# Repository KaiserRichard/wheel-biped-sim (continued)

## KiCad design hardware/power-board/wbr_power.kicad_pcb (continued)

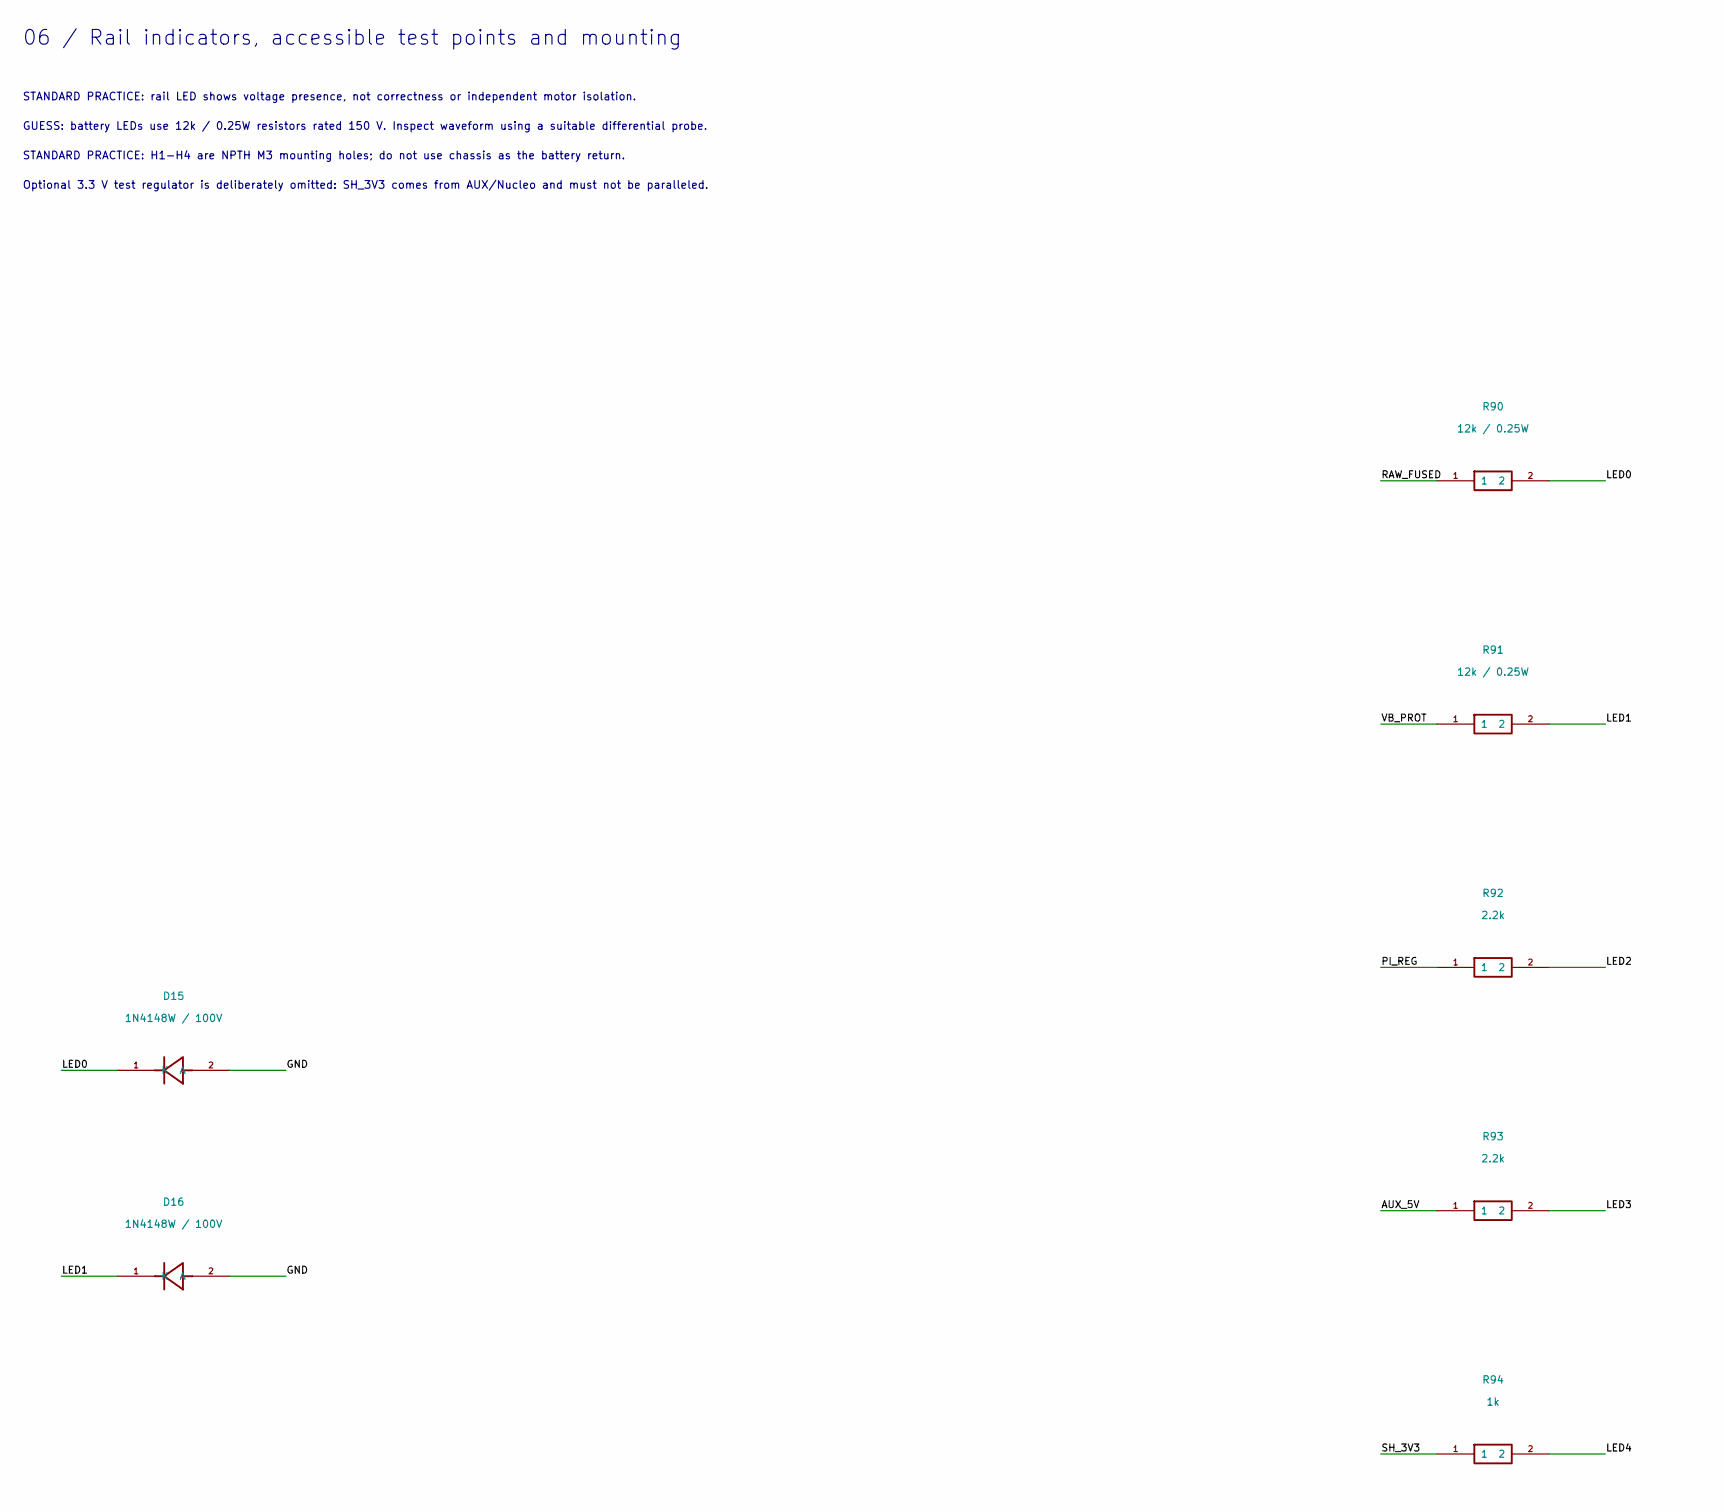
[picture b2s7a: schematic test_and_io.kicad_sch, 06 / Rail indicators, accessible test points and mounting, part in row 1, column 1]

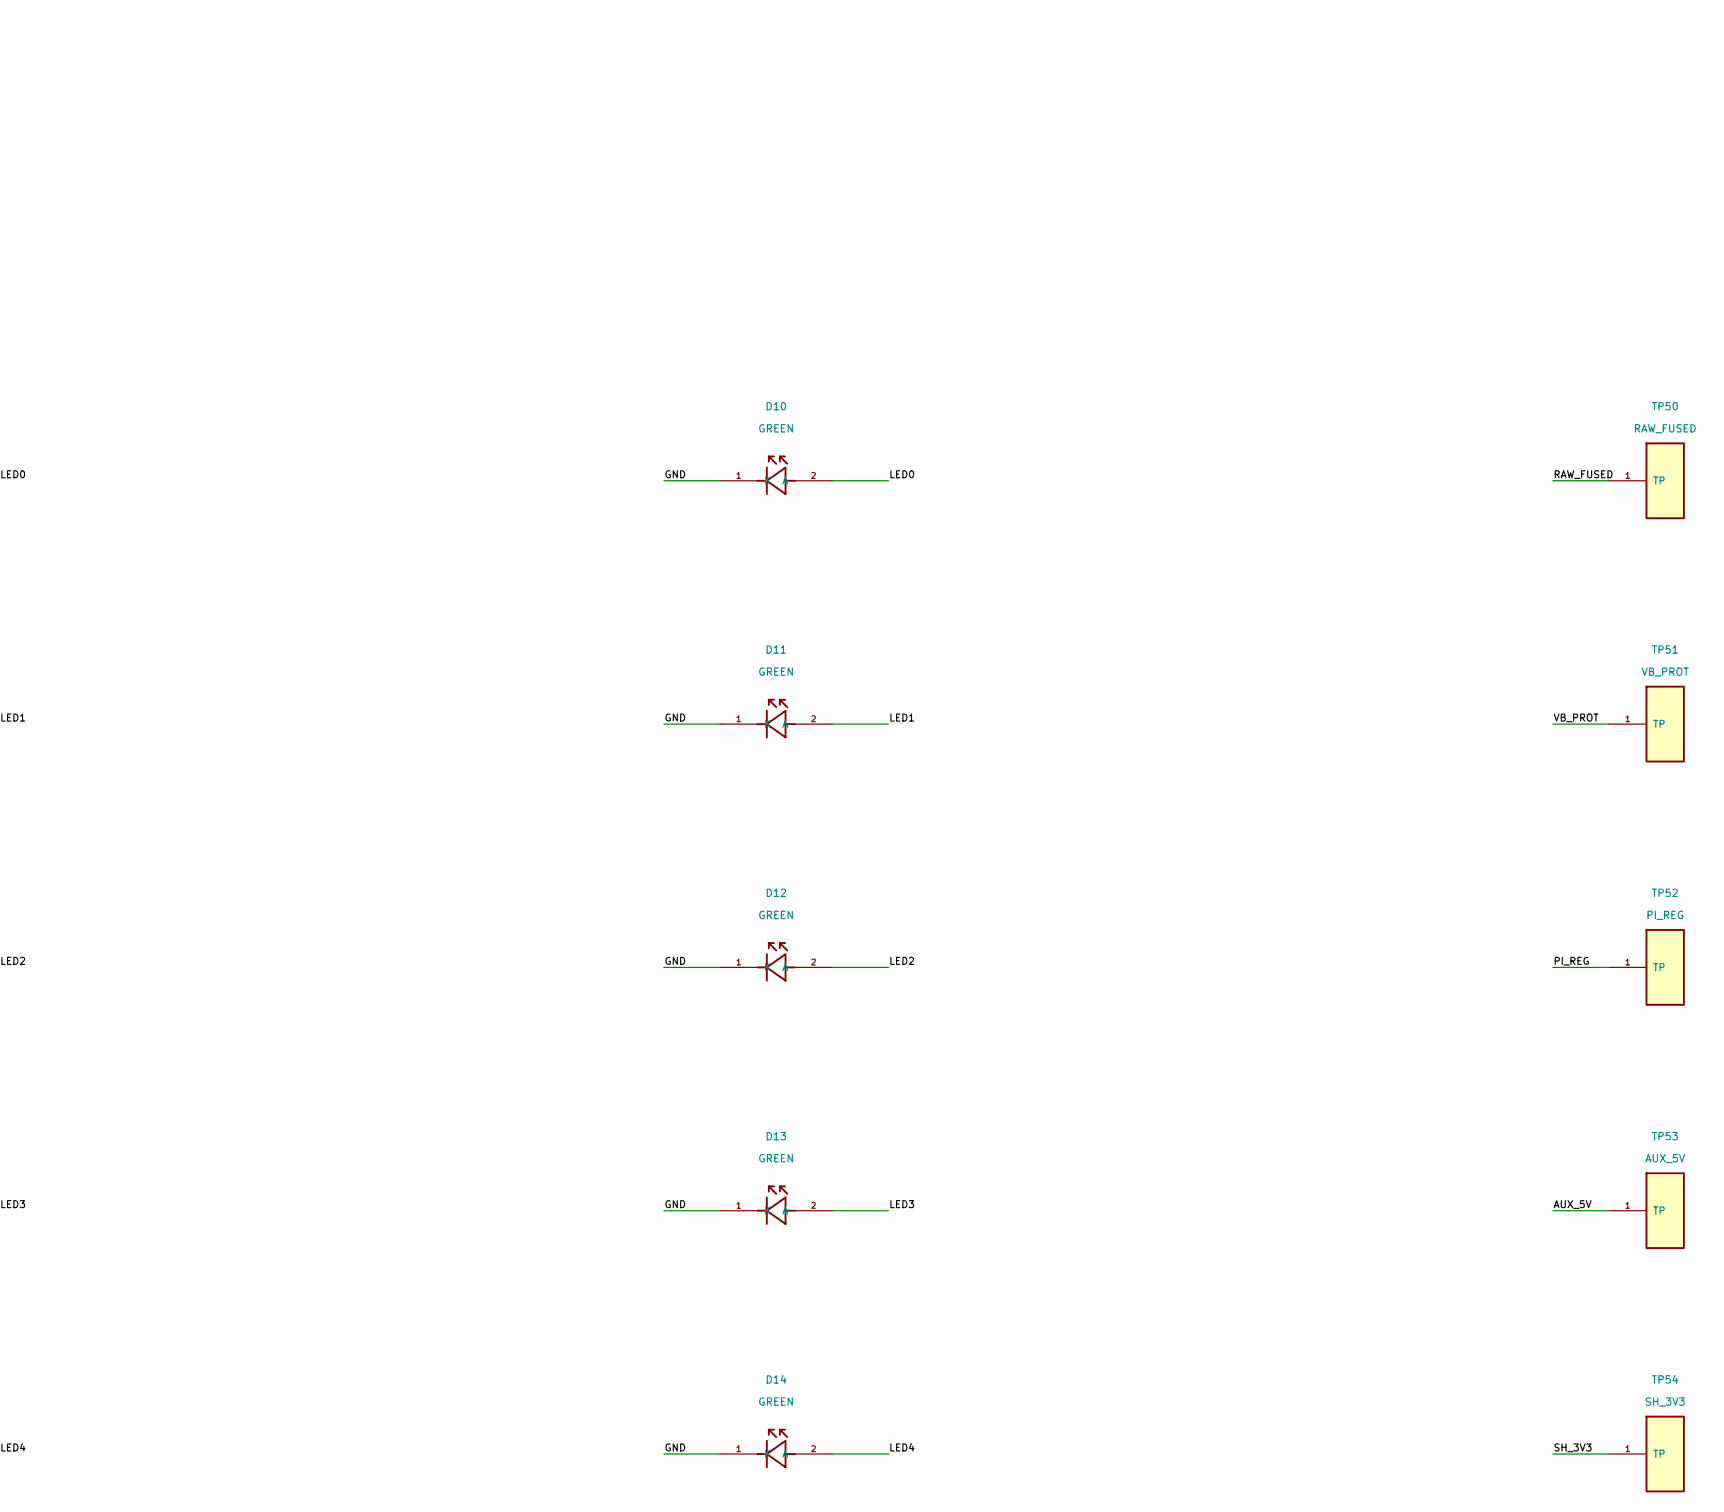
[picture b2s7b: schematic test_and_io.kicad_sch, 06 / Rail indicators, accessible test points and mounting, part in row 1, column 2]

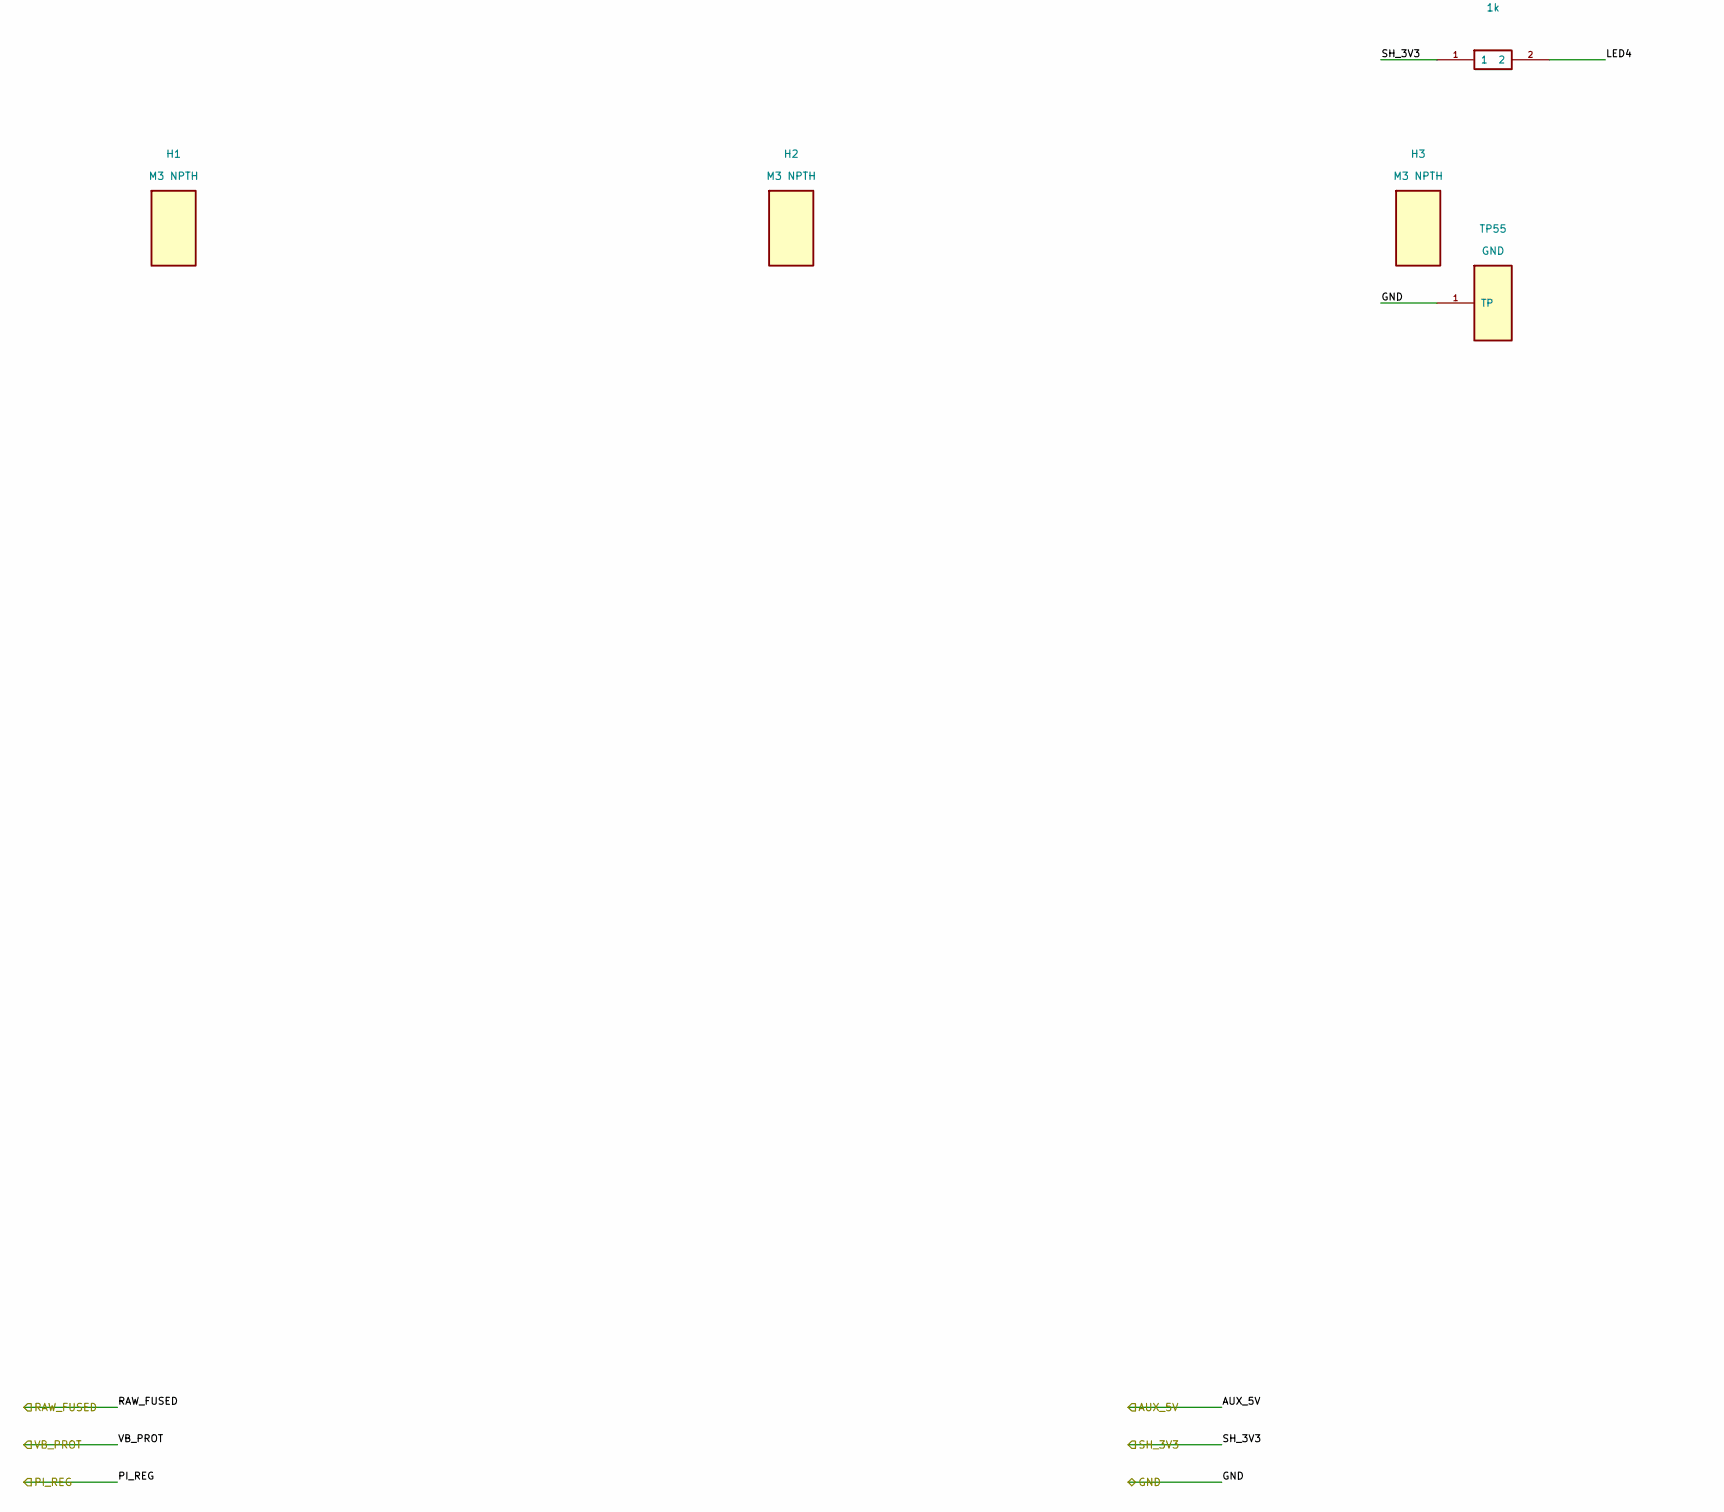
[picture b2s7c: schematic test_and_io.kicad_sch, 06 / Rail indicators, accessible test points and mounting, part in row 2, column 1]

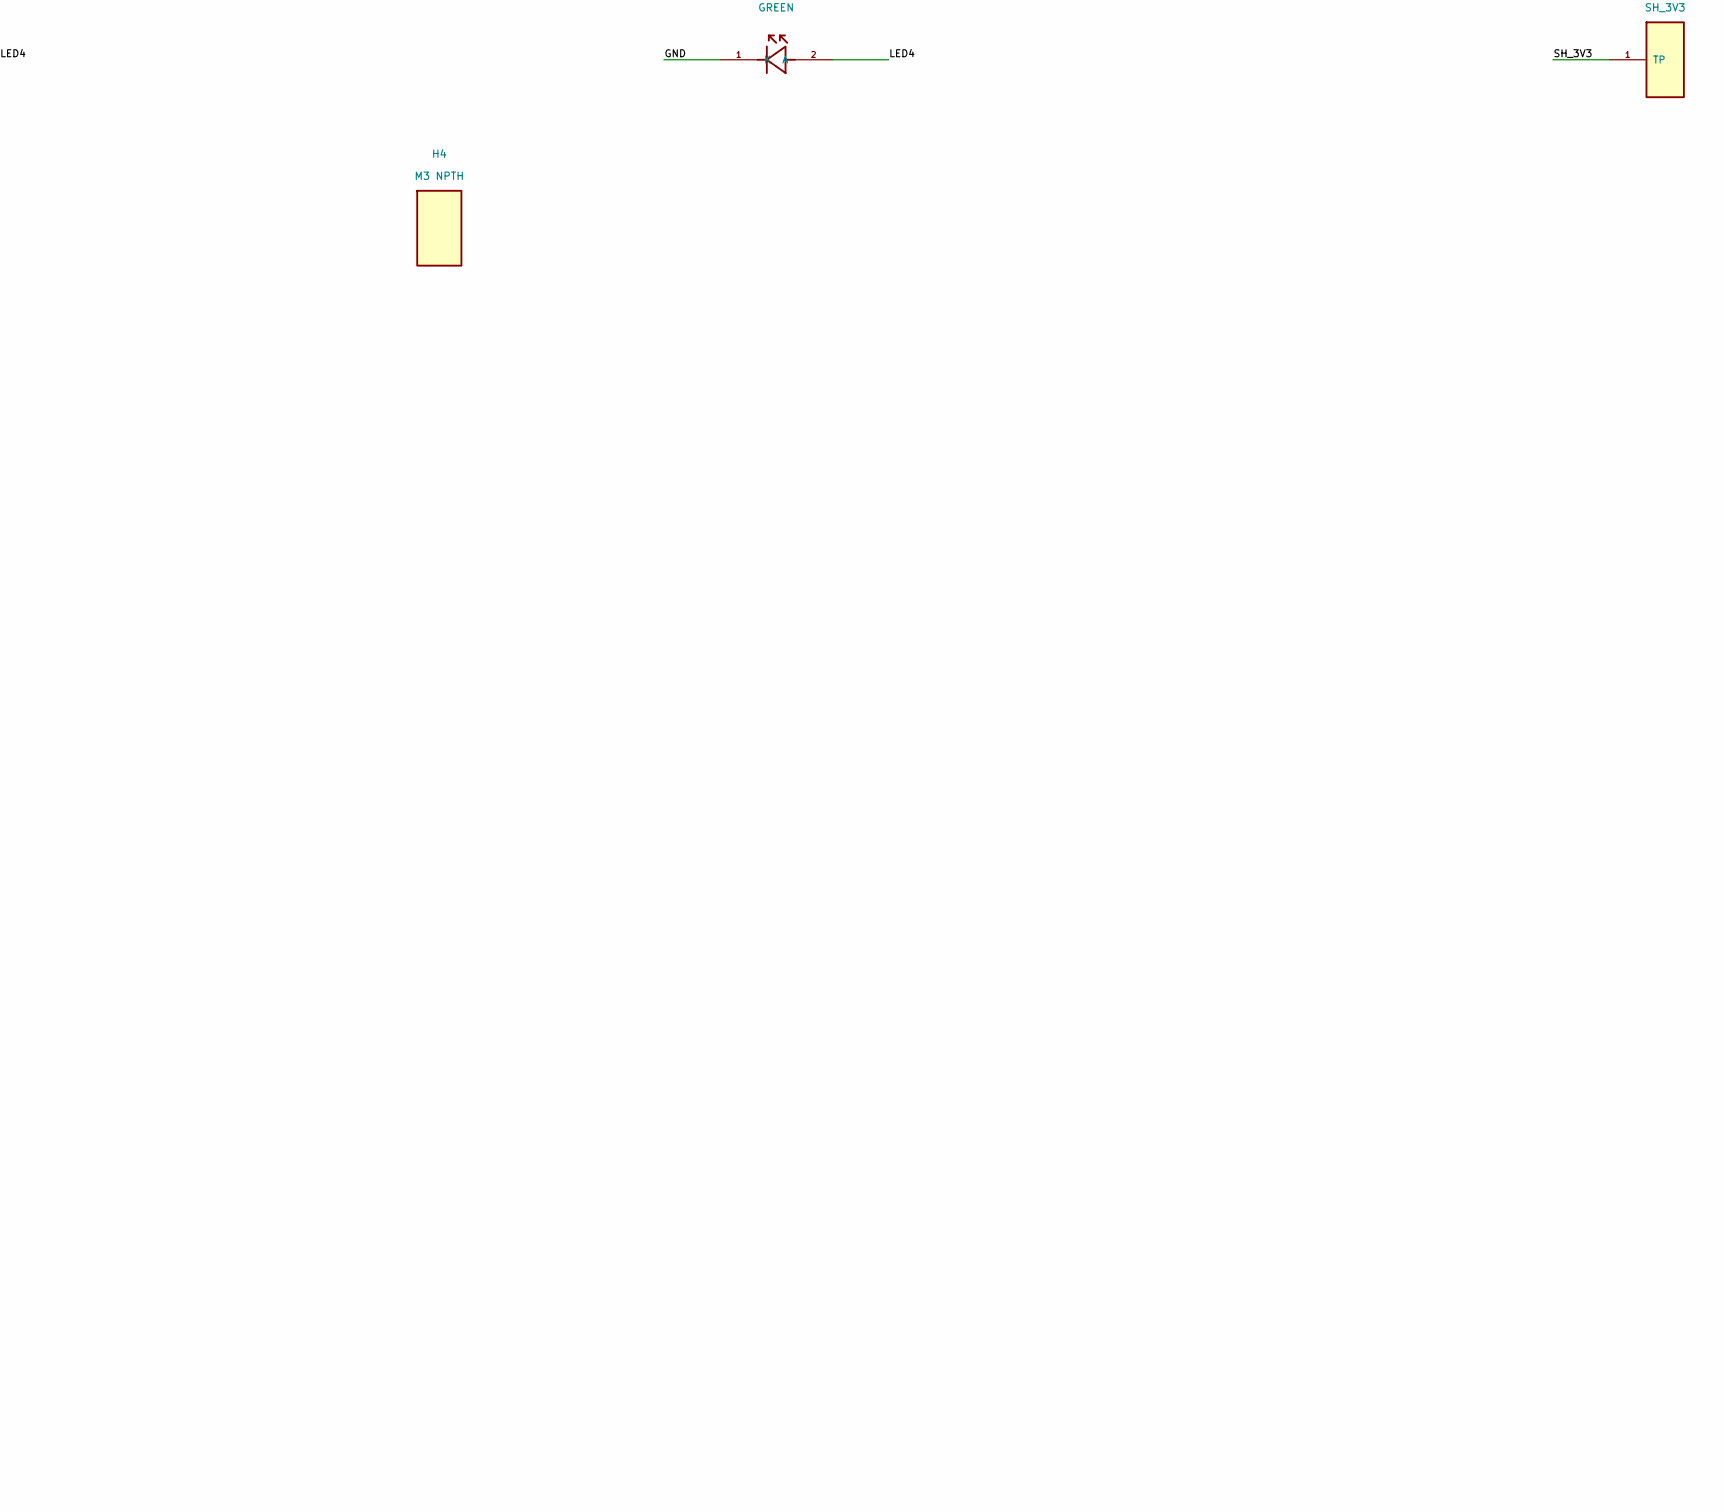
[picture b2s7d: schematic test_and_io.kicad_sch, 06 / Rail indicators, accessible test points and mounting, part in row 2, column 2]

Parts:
D10, D11, D12, D13, D14: GREEN; LED_0805_2012Metric; Rating 2-3 V forward; resistor isolates HV; MPN GREEN
D15: 1N4148W / 100V; D_SOD-123; Rating 100 V; raw LED antiparallel reverse cla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; MPN 1N4148W / 100V
D16: 1N4148W / 100V; D_SOD-123; Rating 100 V; protected LED antiparallel rever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; MPN 1N4148W / 100V
H1, H2, H3, H4: M3 NPTH; MountingHole_3.2mm_M3; Rating 3.2 mm NPTH; MPN M3 NPTH
R90, R91: 12k / 0.25W; R_1206_3216Metric; Rating 150 V; MPN 12k / 0.25W
R92, R93: 2.2k; R_1206_3216Metric; Rating 150 V; MPN 2.2k
R94: 1k; R_1206_3216Metric; Rating 150 V; MPN 1k
TP50: RAW_FUSED; TestPoint_Pad_D2.0mm; Rating >=100 V exposed test pad / voltage as l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; MPN RAW_FUSED
TP51: VB_PROT; TestPoint_Pad_D2.0mm; Rating >=100 V exposed test pad / voltage as l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; MPN VB_PROT
TP52: PI_REG; TestPoint_Pad_D2.0mm; Rating >=100 V exposed test pad / voltage as l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; MPN PI_REG
TP53: AUX_5V; TestPoint_Pad_D2.0mm; Rating >=100 V exposed test pad / voltage as l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; MPN AUX_5V
TP54: SH_3V3; TestPoint_Pad_D2.0mm; Rating >=100 V exposed test pad / voltage as l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; MPN SH_3V3
TP55: GND; TestPoint_Pad_D2.0mm; Rating return reference; MPN GND

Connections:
/AUX_5V: R93.1, TP53.1; also elsewhere on the board
/GND: D10.1 (K), D11.1 (K), D12.1 (K), D13.1 (K), D14.1 (K), D15.2 (A), D16.2 (A), TP55.1; also elsewhere on the board
/PI_REG: R92.1, TP52.1; also elsewhere on the board
/RAW_FUSED: R90.1, TP50.1; also elsewhere on the board
/SH_3V3: R94.1, TP54.1; also elsewhere on the board
/VB_PROT: R91.1, TP51.1; also elsewhere on the board
/test_and_io/LED0: D10.2 (A), D15.1 (K), R90.2
/test_and_io/LED1: D11.2 (A), D16.1 (K), R91.2
/test_and_io/LED2: D12.2 (A), R92.2
/test_and_io/LED3: D13.2 (A), R93.2
/test_and_io/LED4: D14.2 (A), R94.2

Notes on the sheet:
06 / Rail indicators, accessible test points and mounting
STANDARD PRACTICE: rail LED shows voltage presence, not correctness or independent motor isolation.
GUESS: battery LEDs use 12k / 0.25W resistors rated 150 V. Inspect waveform using a suitable differential probe.
STANDARD PRACTICE: H1-H4 are NPTH M3 mounting holes; do not use chassis as the battery return.
Optional 3.3 V test regulator is deliberately omitted: SH_3V3 comes from AUX/Nucleo and must not be paralleled.

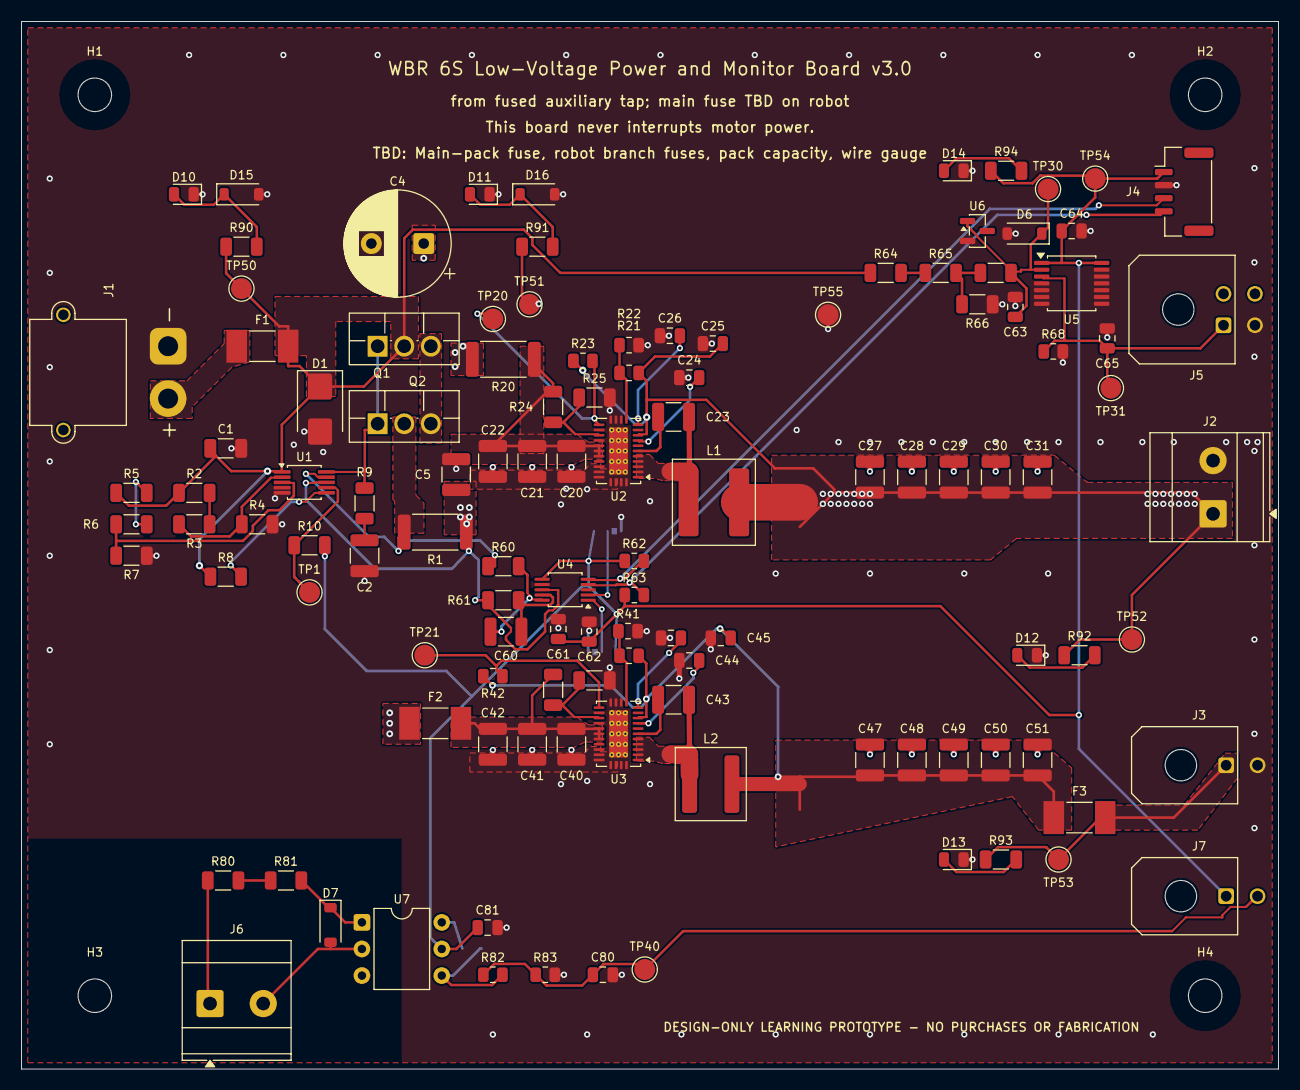
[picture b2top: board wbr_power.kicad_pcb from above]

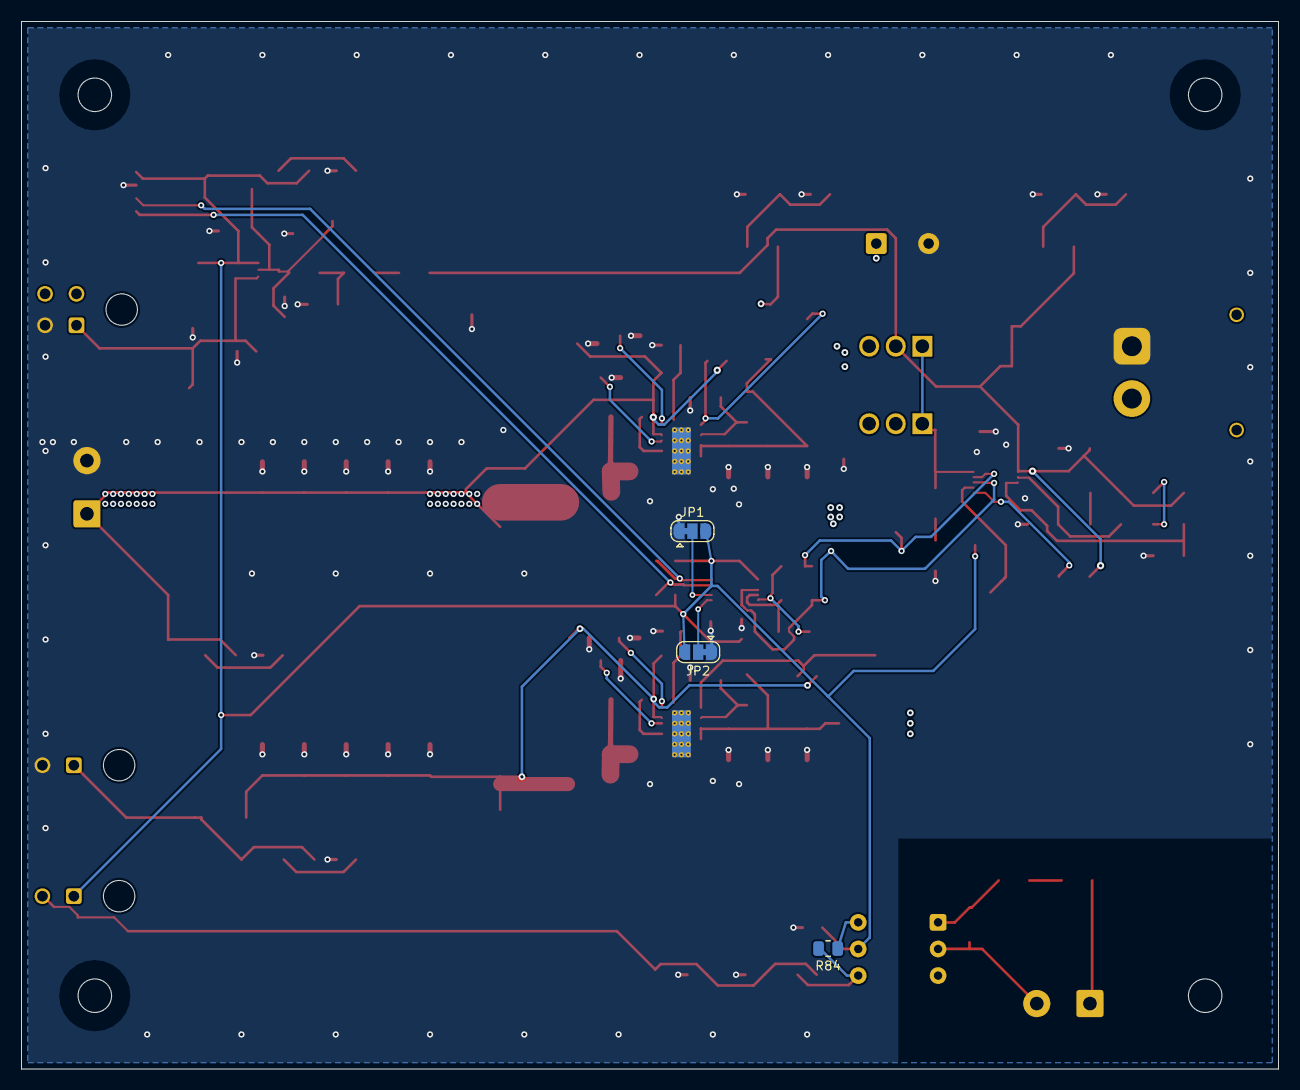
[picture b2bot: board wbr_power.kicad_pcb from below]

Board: 4 copper layers, 120.0 x 100.0 mm, 125 parts (3 on the bottom side), 56 nets.
